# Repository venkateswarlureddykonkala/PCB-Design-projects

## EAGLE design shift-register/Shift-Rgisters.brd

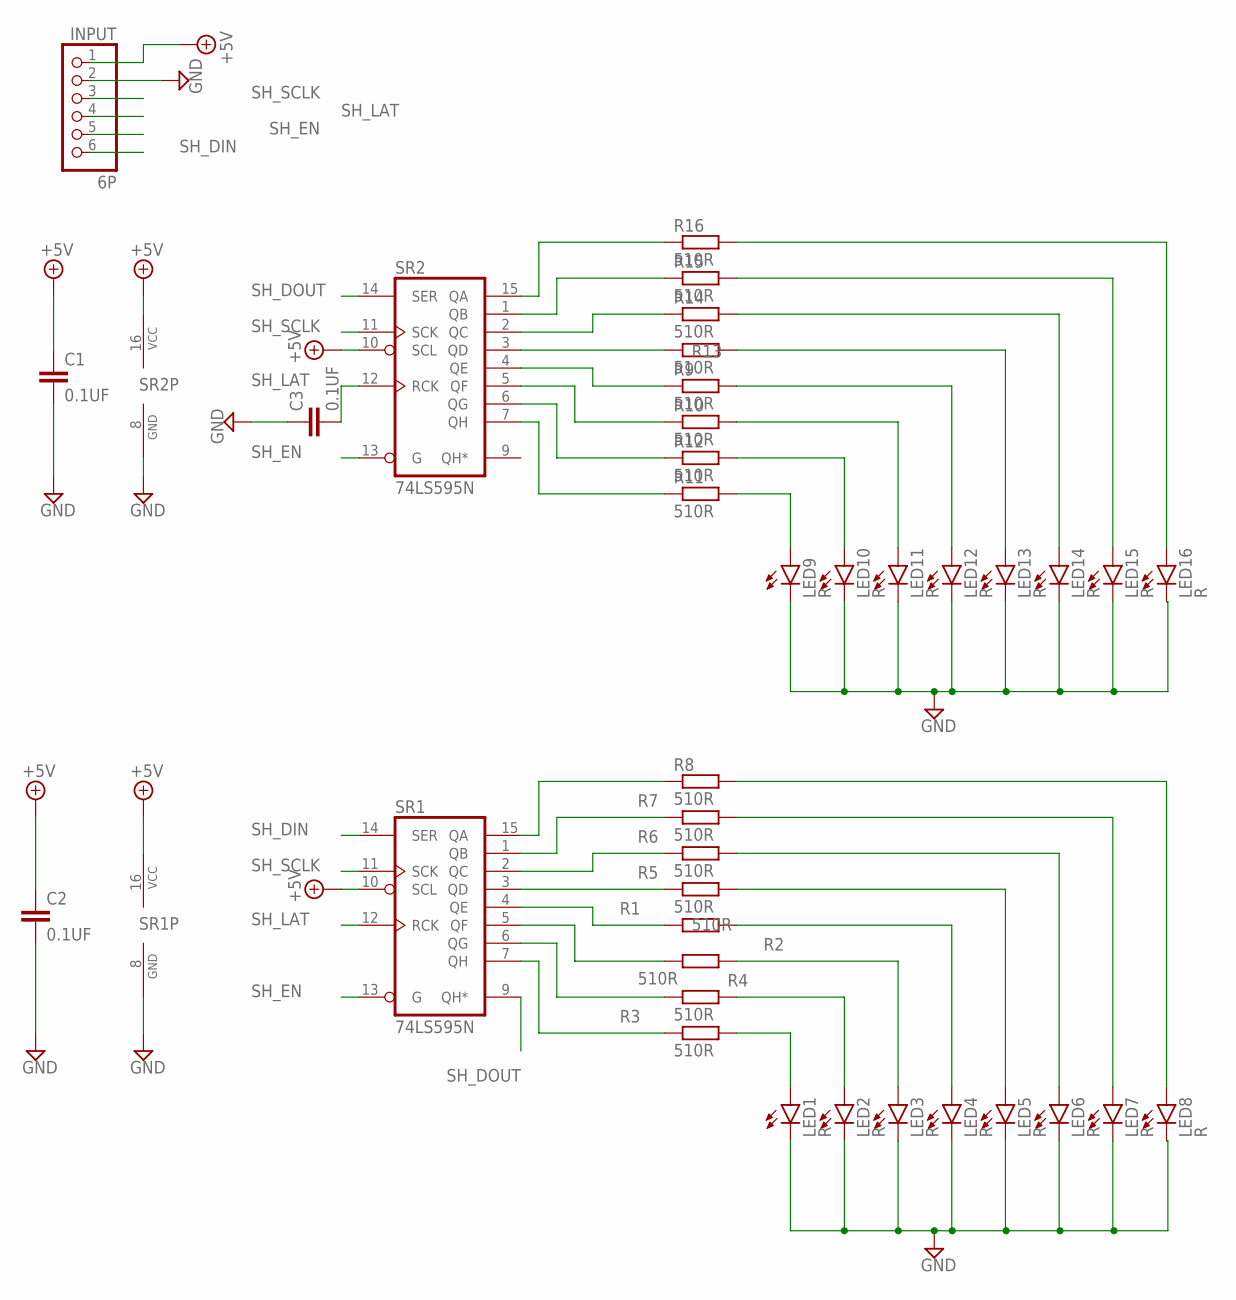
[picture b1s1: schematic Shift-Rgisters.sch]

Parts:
C1, C2, C3: 0.1UF; C050-030X075
INPUT: 6P; 1X06
LED1, LED2, LED3, LED4, LED5, LED6, LED7, LED8, LED9, LED10, LED11, LED12, LED13, LED14, LED15, LED16: R; LED5MM
R1, R2, R3, R4, R5, R6, R7, R8, R9, R10, R11, R12, R13, R14, R15, R16: 510R; 0207/10
SR1, SR2: 74LS595N; DIL16

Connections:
+5V: C1.1, C2.1, INPUT.1, SR1.10 (SCL), SR1.16 (VCC), SR2.10 (SCL), SR2.16 (VCC)
GND: C1.2, C2.2, C3.1, INPUT.2, LED1.K (C), LED2.K (C), LED3.K (C), LED4.K (C), LED5.K (C), LED6.K (C), LED7.K (C), LED8.K (C), LED9.K (C), LED10.K (C), LED11.K (C), LED12.K (C), LED13.K (C), LED14.K (C), LED15.K (C), LED16.K (C), SR1.8 (GND), SR2.8 (GND)
unnamed: R8.1, SR1.15 (QA)
unnamed: R7.1, SR1.1 (QB)
unnamed: R6.1, SR1.2 (QC)
unnamed: R5.1, SR1.3 (QD)
unnamed: R1.1, SR1.4 (QE)
unnamed: R2.1, SR1.5 (QF)
unnamed: R4.1, SR1.6 (QG)
unnamed: R3.1, SR1.7 (QH)
unnamed: LED1.A, R3.2
unnamed: LED2.A, R4.2
unnamed: LED3.A, R2.2
unnamed: LED4.A, R1.2
unnamed: LED5.A, R5.2
unnamed: LED6.A, R6.2
unnamed: LED7.A, R7.2
unnamed: LED8.A, R8.2
unnamed: R16.1, SR2.15 (QA)
unnamed: R15.1, SR2.1 (QB)
unnamed: R14.1, SR2.2 (QC)
unnamed: R13.1, SR2.3 (QD)
unnamed: R9.1, SR2.4 (QE)
unnamed: R10.1, SR2.5 (QF)
unnamed: R12.1, SR2.6 (QG)
unnamed: R11.1, SR2.7 (QH)
unnamed: LED9.A, R11.2
unnamed: LED10.A, R12.2
unnamed: LED11.A, R10.2
unnamed: LED12.A, R9.2
unnamed: LED13.A, R13.2
unnamed: LED14.A, R14.2
unnamed: LED15.A, R15.2
unnamed: LED16.A, R16.2
SH_DIN: INPUT.6, SR1.14 (SER)
SH_DOUT: SR1.9 (QH*), SR2.14 (SER)
SH_EN: INPUT.5, SR1.13 (G), SR2.13 (G)
SH_LAT: C3.2, INPUT.4, SR1.12 (RCK), SR2.12 (RCK)
SH_SCLK: INPUT.3, SR1.11 (SCK), SR2.11 (SCK)

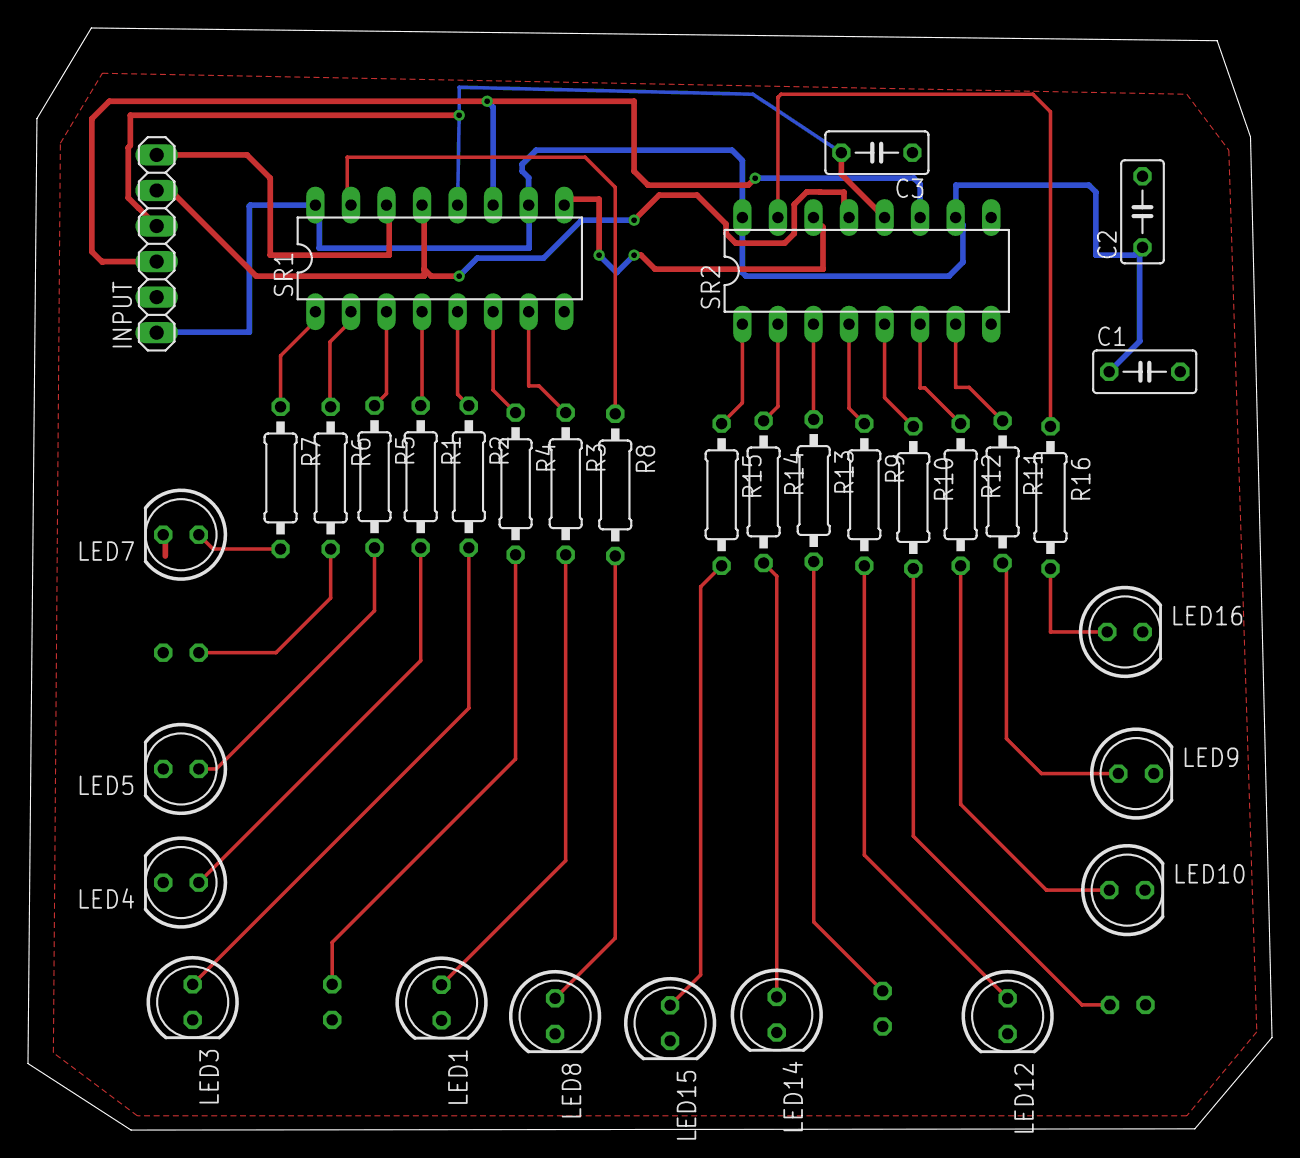
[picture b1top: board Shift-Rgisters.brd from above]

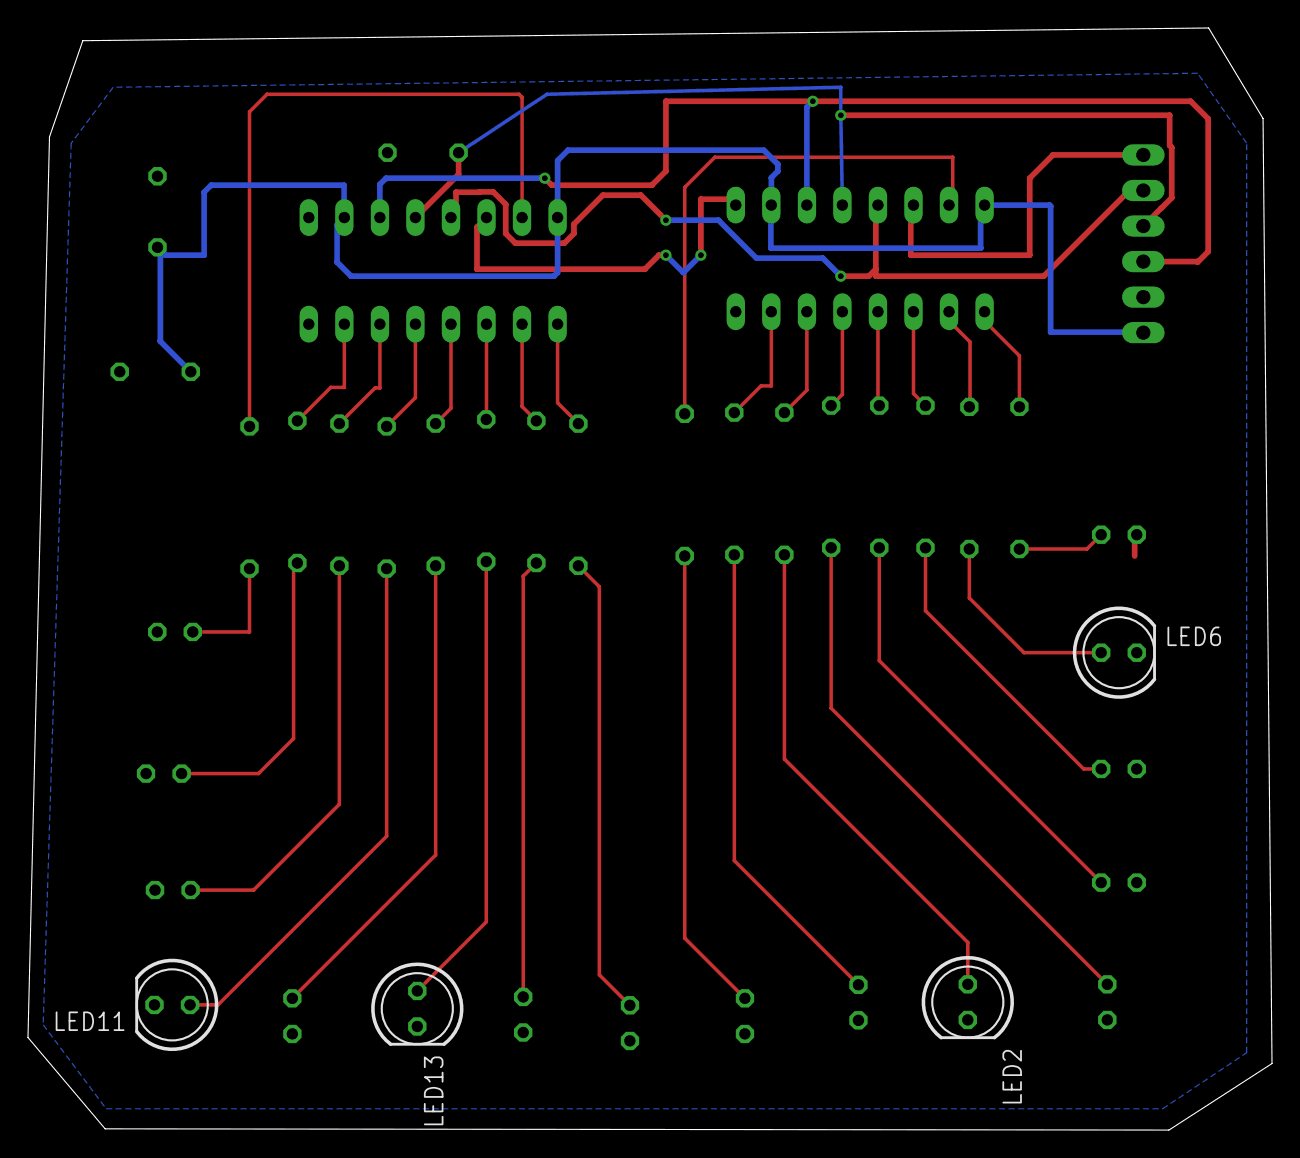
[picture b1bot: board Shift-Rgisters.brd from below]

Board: 2 copper layers, 88.9 x 78.8 mm, 38 parts (4 on the bottom side), 39 nets.

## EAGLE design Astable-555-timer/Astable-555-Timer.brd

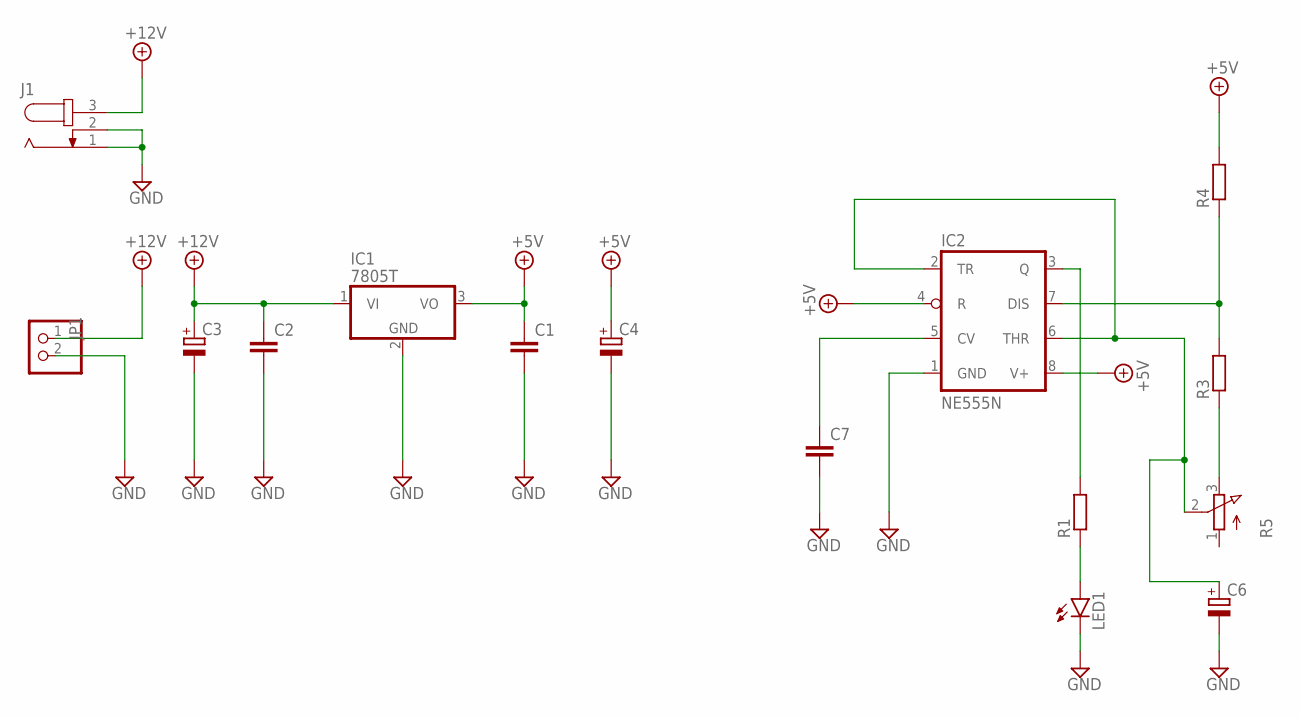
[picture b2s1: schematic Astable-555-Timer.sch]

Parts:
C1, C2, C7: C-EU050-030X075; C050-030X075
C3, C4, C6: CPOL-EUE3.5-8; E3,5-8
IC1: 7805T; TO220H
IC2: NE555N; DIL08
J1: JACK-PLUG1; SPC4078
JP1: PINHD-1X2; 1X02
LED1: LED5MM
R1, R3, R4: R-EU_0207/10; 0207/10
R5: 3RP/1610N

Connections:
+5V: C1.1, C4.+, IC1.3 (VO), IC2.4 (R), IC2.8 (V+), R4.2
+12V: C2.1, C3.+, IC1.1 (VI), J1.3, JP1.1
GND: C1.2, C2.2, C3.-, C4.-, C6.-, C7.2, IC1.2 (GND), IC2.1 (GND), J1.1, J1.2, JP1.2, LED1.K (C)
unnamed: C7.1, IC2.5 (CV)
unnamed: C6.+, IC2.2 (TR), IC2.6 (THR), R5.2 (S)
unnamed: IC2.7 (DIS), R3.2, R4.1
unnamed: R3.1, R5.3 (E)
unnamed: LED1.A, R1.1
unnamed: IC2.3 (Q), R1.2

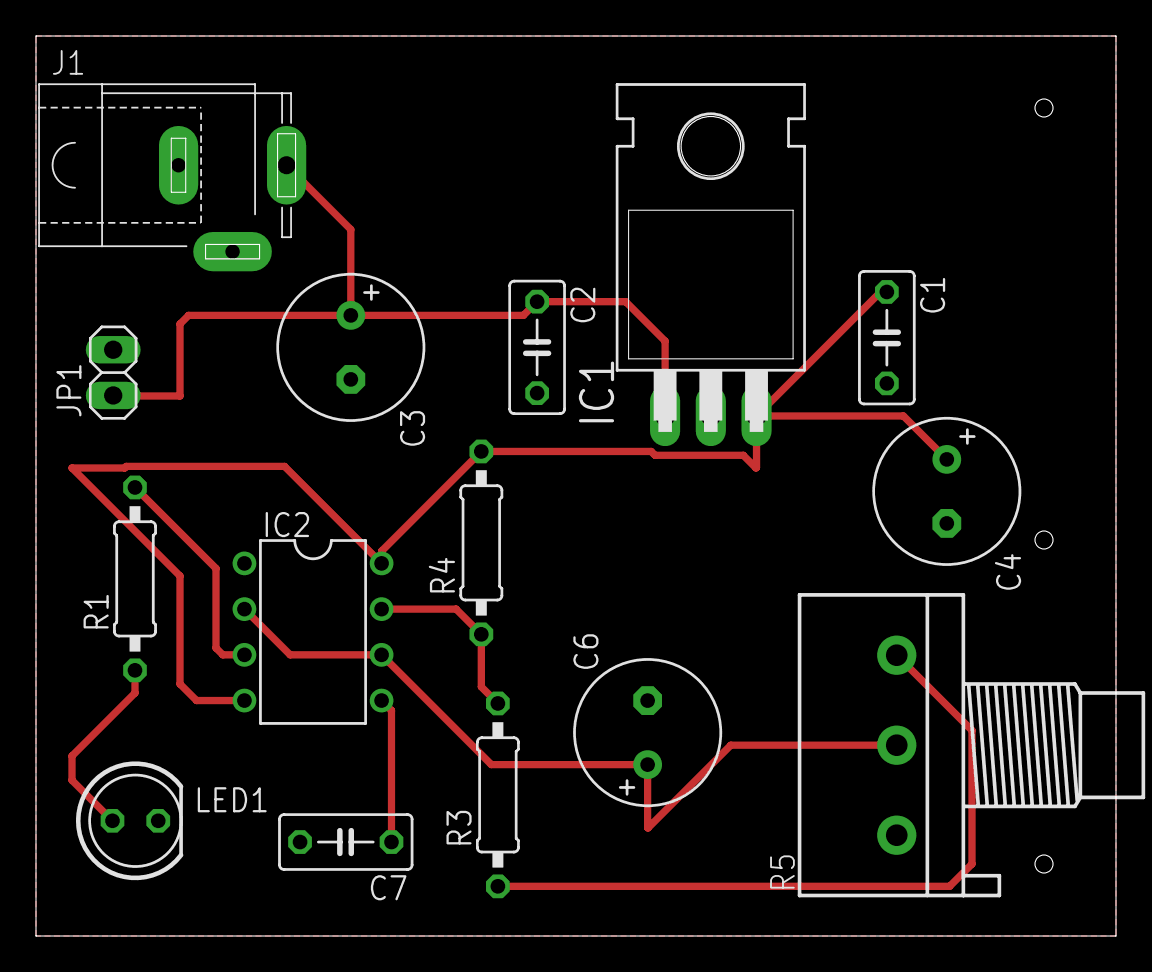
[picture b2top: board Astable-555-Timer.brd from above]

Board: 2 copper layers, 60.0 x 50.0 mm, 15 parts (0 on the bottom side), 9 nets.
